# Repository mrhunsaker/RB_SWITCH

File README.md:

# RB Switch

The RB Switch is a three-button Bluetooth Low Energy (BLE) accessibility switch. It presents itself to a computer, tablet, or phone as a standard Bluetooth keyboard, so it works with Switch Control (iOS/iPadOS), Switch Access (Android), and any app that accepts keyboard input.

## At a glance

| | |
|---|---|
| **Buttons** | SW1 Left Arrow, SW2 Enter, SW3 Right Arrow |
| **Bluetooth name** | RB Switch |
| **Microcontroller** | ESP32-S3-MINI-1-N4R2 |
| **Power** | USB-C or a single-cell Li-Po battery. No power switch and no sleep mode. |
| **Charging** | MCP73831, about 500 mA. D1 lights while charging. |
| **Regulator** | TPS63001 3.3 V buck-boost |
| **PCB** | KiCad 10, 4 layers, 115 × 38 mm |
| **Firmware** | Arduino sketch using NimBLE-Arduino 2.x |

## Quick start

1. Power the switch from USB-C or its battery.
2. Pair **RB Switch** in the device's Bluetooth settings.
3. Press each button in a text field: Left, Enter, Right.
4. Set up Switch Control (iOS/iPadOS) or Switch Access (Android) from the guides below.

**Important for Android users:** Android's Switch Access is a separate app you install/update from the Google Play Store, and its setup wizard only offers a one-switch or two-switch configuration. It does not offer a third switch by default. Using the RB Switch's third button on Android requires one extra step beyond the wizard. This is different from iOS/iPadOS, where all three buttons can be assigned directly in the normal setup flow. See [Android Switch Access](docs/switch-access-android.md) and [iOS/iPadOS Switch Control](docs/switch-control-ios.md) before you configure a device.

## Production firmware

The production firmware is:

`firmware/RB_SWITCH_firmware/RB_SWITCH_firmware.ino`

### Button mapping

| Switch | GPIO   | Keyboard key |
| ------ | ------:| ------------ |
| SW1    | GPIO10 | Left Arrow   |
| SW2    | GPIO11 | Enter        |
| SW3    | GPIO12 | Right Arrow  |

Each button press produces one key press followed by one key release. Holding a button does not repeat the key. A press made while no host is connected is ignored.

### Building the firmware

1. Install the Arduino IDE, the **ESP32 Arduino core** by Espressif, and **NimBLE-Arduino 2.x**.
2. Select **ESP32S3 Dev Module** and set **USB CDC On Boot** to **Enabled**.
3. Open the `.ino` file, click **Verify**, then **Upload** over a data-capable USB-C cable. If the upload does not start, hold BOOT, tap RESET, release BOOT.
4. Open the Serial Monitor at 115200 baud.

See [Firmware](docs/firmware.md) for details.

## Documentation

| For | Read |
|---|---|
| Classroom staff setting up a device | [Setup & Pairing](docs/setup.md) |
| iPad and iPhone | [iOS/iPadOS Switch Control](docs/switch-control-ios.md) |
| Android phones and tablets | [Android Switch Access](docs/switch-access-android.md) |
| How the buttons behave | [Switch Operation](docs/use.md) |
| Something is not working | [Troubleshooting](docs/troubleshooting.md) |
| Evaluating a student for switch access and teaching switch skills | [Switch Evaluation Package](docs/evaluation-package.md) |
| Programming the board | [Firmware](docs/firmware.md), [Firmware Customization](docs/firmware-customization.md) |
| Hardware reference | [Hardware](docs/hardware.md) |
| Enclosure label | [QR Code](docs/qr-code.md) |

Published documentation: <https://mrhunsaker.github.io/RB_SWITCH/>

Two printable Word documents are also available. Both are generated from the matching page in `docs/`.

| Download | Source page | Use |
|---|---|---|
| [`RB_Switch_Paraprofessional_Setup_Guide.docx`](RB_Switch_Paraprofessional_Setup_Guide.docx) | `docs/setup.md` | Classroom quick-reference for pairing, setup and troubleshooting |
| [`RB_Switch_Evaluation_Package.docx`](RB_Switch_Evaluation_Package.docx) | `docs/evaluation-package.md` | Fill-in package for evaluating, teaching and documenting adaptive switch access (checklists, five-stage data sheets, graphing sheet, summary report, IEP goal bank) |

## Troubleshooting at a glance

| Symptom | First thing to try |
|---|---|
| Not in the Bluetooth list | Check power; turn Bluetooth off on other nearby devices that were paired before |
| Listed but will not connect | Forget RB Switch on the device and pair again |
| Connected, but no button works | Check it still shows Connected; a press made while disconnected is lost |
| Only two buttons work on Android | Assign the third switch under Assign switches for scanning |
| Will not power on | Charge from USB-C for 30 minutes with a known-good cable |
| Upload fails or no serial port | Hold BOOT, tap RESET, release BOOT; use a data cable |

The full guide, including board-level checks for technicians, is in [Troubleshooting](docs/troubleshooting.md).

## Hardware

The current board uses:

- ESP32-S3-MINI-1-N4R2
- Three Omron B3F-series tactile switches
- USB-C power/programming connection (native USB, no USB-to-serial chip)
- Single-cell Li-Po battery connection and MCP73831 charger
- TPS63001 3.3 V buck-boost regulator
- Battery-voltage sensing (not yet used by the firmware)
- MCP73831 charge-status LED
- Reset and boot buttons, with a 10 kΩ pull-up and 1 µF capacitor on the reset line

Hardware source files are in `electrical/`, `bom/`, and `mechanical/`.

| Path | Contents |
|---|---|
| `electrical/mechanical_switch/RB_Switch.kicad_sch`, `.kicad_pcb` | Current KiCad 10 schematic and 4-layer PCB. The schematic is fully wired and its netlist matches the PCB. |
| `electrical/mechanical_switch/VERIFICATION.md` | How the board was checked against the firmware, and what was not checked |
| `electrical/mechanical_switch/net_table.json` | Net-by-net list of pads |
| `bom/` | BOMs and placement files for JLCPCB and PCBWay, plus sourcing notes |
| `mechanical/` | Enclosure (OpenSCAD) |
| `docs/hardware.md` | Pin map and a part-by-part description of the connections |

> **Before ordering boards:** the files in `electrical/mechanical_switch/gerbers/` and the PCB images in `electrical/mechanical_switch/diagrams/` come from an earlier layout. Re-export them with `create_gerber.ps1` and check the CPL orientation of U1, REG1, D1, J_USB1, and L1 in the fab's preview.

## Production scope

The production design has three mechanical switch inputs only. It does not implement touch sensors, proximity sensors, NeoPixel/RGB indicators, mono-jack inputs, or the earlier F-key input mapping.

The charge-status LED (D1) is controlled by the battery charger and is not a programmable RGB LED.

## Repository layout

| Path | Contents |
|---|---|
| `firmware/RB_SWITCH_firmware/` | Production sketch |
| `firmware/BLE_ADAPTIVE_SWITCH_EXPANDED_SCAFFOLD/` | Archived earlier firmware, not production |
| `electrical/` | KiCad project, gerbers, diagrams, verification notes |
| `bom/` | BOM, placement and sourcing files |
| `mechanical/` | Enclosure and storage box models |
| `docs/` | GitHub Pages source |
| `documents/` | Packaging-friendly copy of `docs/` |
| `tools/` | Scripts that keep `documents/` and the printable Word documents in sync with `docs/` |
| `RB_Switch_Paraprofessional_Setup_Guide.docx` | Printable classroom guide |
| `RB_Switch_Evaluation_Package.docx` | Printable switch evaluation package |
| `CHANGES.md` | Changelog |

## Documentation source

`docs/` is the published GitHub Pages source.

`documents/` contains the same documentation in a packaging-friendly directory. Keep the two documentation sets synchronized when documentation changes.

After editing `docs/`, run:

```
python3 tools/sync_documents.py
node tools/build_docx.js
```

The first script rewrites `documents/` from `docs/`. The second rebuilds both Word documents (`RB_Switch_Paraprofessional_Setup_Guide.docx` from `docs/setup.md` and `RB_Switch_Evaluation_Package.docx` from `docs/evaluation-package.md`). It needs Node.js and the `docx` package (`npm install docx`). Pass `setup` or `evaluation` to build just one. See [tools/README.md](tools/README.md).

## GitHub Pages and enclosure QR code

Publish `docs/` with GitHub Pages. The enclosure QR code should point to the published documentation home page. See [QR Code](docs/qr-code.md).

## Contributing

Contributions to firmware, hardware, and documentation are welcome. See [CONTRIBUTING.md](CONTRIBUTING.md) for project structure, how to propose a change, and pull request expectations, and [CODE_STYLE.md](CODE_STYLE.md) for formatting and naming conventions. Please review [CODE_OF_CONDUCT.md](CODE_OF_CONDUCT.md) before participating.

## Security

To report a suspected security or safety issue, see [SECURITY.md](SECURITY.md) rather than opening a public issue.

## Changelog

See [CHANGES.md](CHANGES.md) for a history of notable changes.

## License

This project is licensed under the APACHE 2.0 License— see [LICENSE](LICENSE) for the full text, including a note on hardware-specific licensing alternatives.

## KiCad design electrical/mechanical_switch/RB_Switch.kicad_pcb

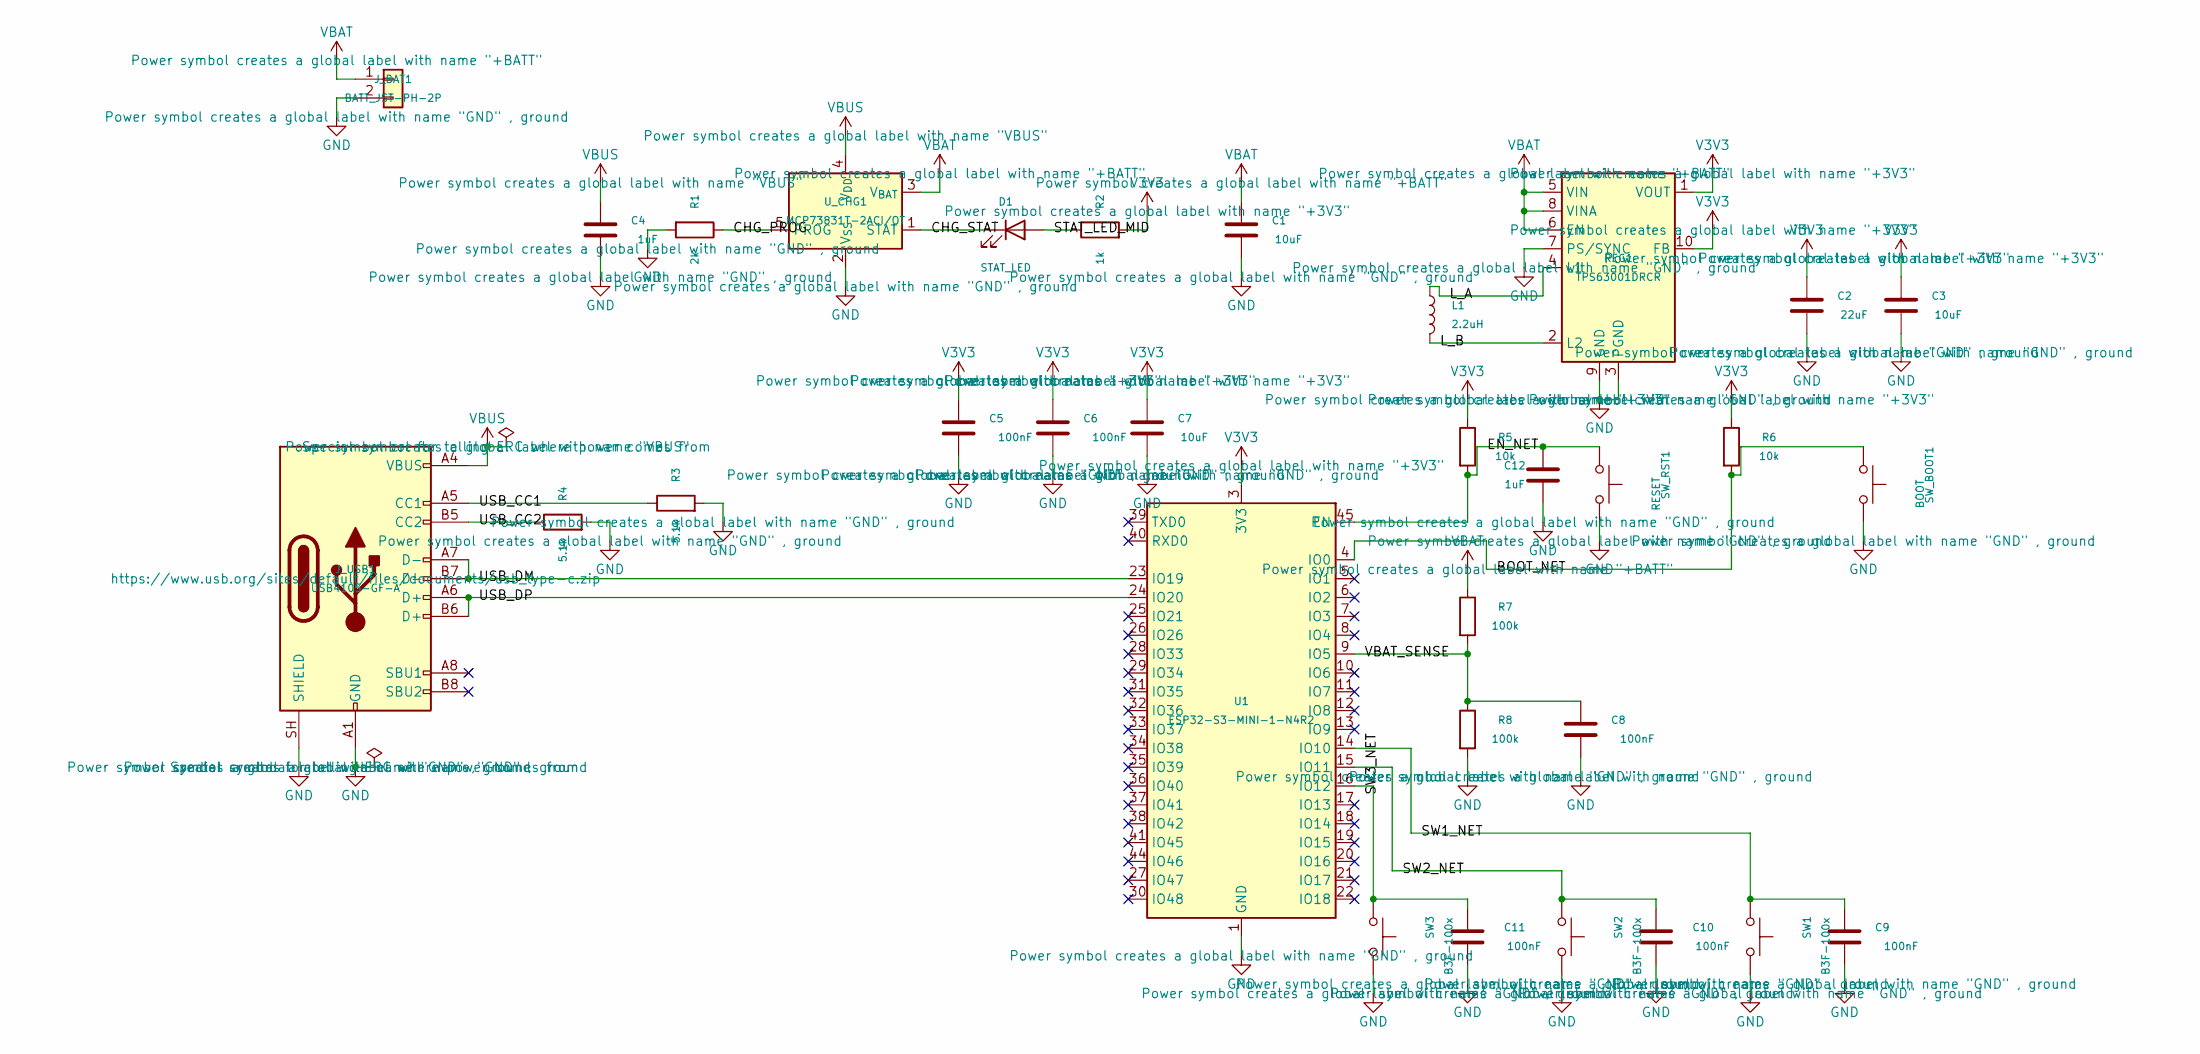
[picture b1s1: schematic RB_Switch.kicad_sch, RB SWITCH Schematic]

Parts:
C1, C3, C7: 10uF; C_0603_1608Metric
C2: 22uF; C_0603_1608Metric
C4, C12: 1uF; C_0603_1608Metric
C5, C6, C8, C9, C10, C11: 100nF; C_0603_1608Metric
D1: STAT_LED; LED_0603_1608Metric
J_BAT1: BATT_JST-PH-2P; JST_PH_S2B-PH-K_1x02_P2.00mm_Horizontal
J_USB1: USB4105-GF-A; USB_C_Receptacle_GCT_USB4105-xx-A_16P_TopMnt_Horizontal
L1: 2.2uH; L_Bourns-SRN4018
R1: 2k; R_0603_1608Metric
R2: 1k; R_0603_1608Metric
R3, R4: 5.1k; R_0603_1608Metric
R5, R6: 10k; R_0603_1608Metric
R7, R8: 100k; R_0603_1608Metric
REG1: TPS63001DRCR; Texas_DRC0010J
SW1, SW2, SW3: B3F-100x; SW_TH_Tactile_Omron_B3F-100x
SW_BOOT1: BOOT; SW_SPST_B3U-1000P
SW_RST1: RESET; SW_SPST_B3U-1000P
U1: ESP32-S3-MINI-1-N4R2; ESP32-S2-MINI-1
U_CHG1: MCP73831T-2ACI/OT; SOT-23-5

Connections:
/BOOT_NET: R6.2, SW_BOOT1.1, U1.4 (IO0)
/CHG_PROG: R1.1, U_CHG1.5 (PROG)
/CHG_STAT: D1.1 (K), U_CHG1.1 (STAT)
/EN_NET: C12.1, R5.2, SW_RST1.1, U1.45 (EN)
/L_A: L1.1, REG1.4 (L1)
/L_B: L1.2, REG1.2 (L2)
/STAT_LED_MID: D1.2 (A), R2.1
/SW1_NET: C9.1, SW1.1, U1.14 (IO10)
/SW2_NET: C10.1, SW2.1, U1.15 (IO11)
/SW3_NET: C11.1, SW3.1, U1.16 (IO12)
/USB_CC1: J_USB1.A5 (CC1), R3.1
/USB_CC2: J_USB1.B5 (CC2), R4.1
/USB_DM: J_USB1.A7 (D-), J_USB1.B7 (D-), U1.23 (IO19)
/USB_DP: J_USB1.A6 (D+), J_USB1.B6 (D+), U1.24 (IO20)
/VBAT_SENSE: C8.1, R7.2, R8.1, U1.9 (IO5)
GND: C1.2, C2.2, C3.2, C4.2, C5.2, C6.2, C7.2, C8.2, C9.2, C10.2, C11.2, C12.2, J_BAT1.2, J_USB1.A1 (GND), J_USB1.A12 (GND), J_USB1.B1 (GND), J_USB1.B12 (GND), J_USB1.SH (SHIELD), R1.2, R3.2, R4.2, R8.2, REG1.3 (PGND), REG1.7 (PS/SYNC), REG1.9 (GND), REG1.11 (PGND), SW1.2, SW2.2, SW3.2, SW_BOOT1.2, SW_RST1.2, U1.1 (GND), U1.2 (GND), U1.42 (GND), U1.43 (GND), U1.46 (GND), U1.47 (GND), U1.48 (GND), U1.49 (GND), U1.50 (GND), U1.51 (GND), U1.52 (GND), U1.53 (GND), U1.54 (GND), U1.55 (GND), U1.56 (GND), U1.57 (GND), U1.58 (GND), U1.59 (GND), U1.60 (GND), U1.61 (GND), U1.62 (GND), U1.63 (GND), U1.64 (GND), U1.65 (GND), U_CHG1.2 (V_{SS})
V3V3: C2.1, C3.1, C5.1, C6.1, C7.1, R2.2, R5.1, R6.1, REG1.1 (VOUT), REG1.10 (FB), U1.3 (3V3)
VBAT: C1.1, J_BAT1.1, R7.1, REG1.5 (VIN), REG1.6 (EN), REG1.8 (VINA), U_CHG1.3 (V_{BAT})
VBUS: C4.1, J_USB1.A4 (VBUS), J_USB1.A9 (VBUS), J_USB1.B4 (VBUS), J_USB1.B9 (VBUS), U_CHG1.4 (V_{DD})

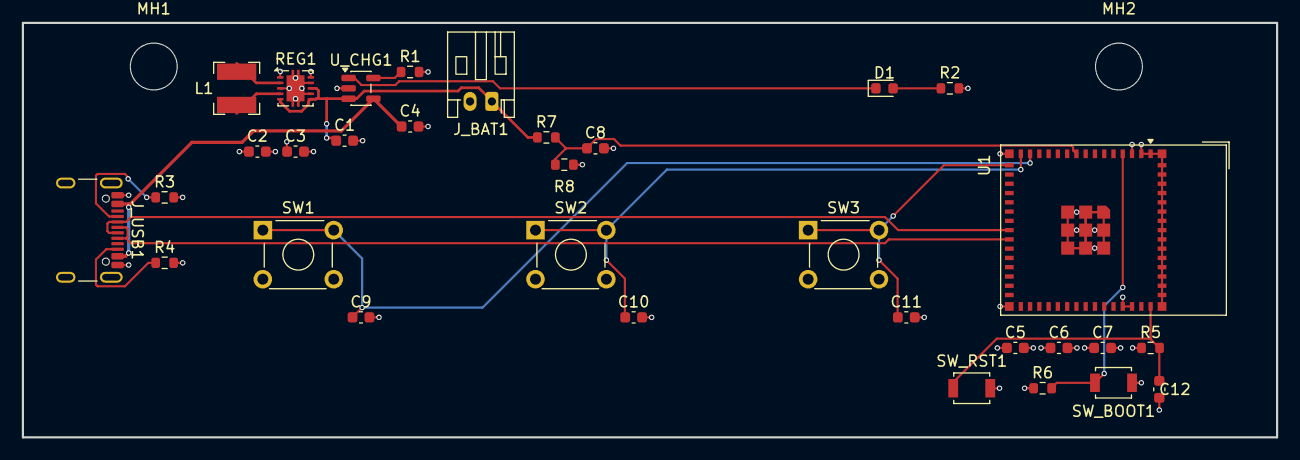
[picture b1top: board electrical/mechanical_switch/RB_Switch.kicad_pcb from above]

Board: 4 copper layers, 115.0 x 38.0 mm, 34 parts (0 on the bottom side), 19 nets.

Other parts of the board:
MH1, MH2: MountingHole; MountingHole_4.3mm_M4

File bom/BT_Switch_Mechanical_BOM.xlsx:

Ref Des | Description | Manufacturer | Part Number | Package / Footprint | Qty | Notes
CORE / MCU
U1 | MCU module — WiFi/BLE SoC, 4MB flash, 2MB PSRAM | Espressif | ESP32-S3-MINI-1-N4R2 | SMD castellated module (RF_Module:ESP32-S2-MINI-1 land pattern) | 1 | Land pattern shared with ESP32-S2-MINI-1 per Espressif; confirmed in KiCad foot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
POWER — REGULATION & CHARGING
REG1 | Buck-boost regulator, fixed 3.3V out, 1.7A switch current | Texas Instruments | TPS63001DRCR | VSON-10 (Package_SON:Texas_DRC0010J_ThermalVias) | 1 | Single-cell Li-ion buck-boost; handles ESP32-S3 BLE TX current peaks with margi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
U_CHG | Li-ion linear charge management IC, USB input | Microchip | MCP73831T-2ACI/OT | SOT-23-5 | 1 | ADDED vs. original BOM — battery + USB-C strongly implies charging; flagged as 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
L1 | Inductor, 2.2uH, shielded | Bourns | SRN4018-2R2Y | SMD 4x4mm | 1 | Buck-boost inductor (single inductor, L1/L2 pins of REG1).
D1 | Charge-status LED | Generic (e.g. Kingbright) | APT2012xx-series or equiv. | 0603 SMD | 1 | Lit while charging (STAT pin, open-drain).
C1 | Capacitor, 10uF, X5R, 10V | Generic | — | 0603 | 1 | REG1 input.
C2 | Capacitor, 22uF, X5R, 10V | Generic | — | 0805 (may not fit 0603 at this voltage rating) | 1 | REG1 output; confirm 0603 X5R 22uF/10V availability, else use 0805.
C3 | Capacitor, 10uF, X5R, 10V | Generic | — | 0603 | 1 | 3V3 rail bulk decoupling.
C4 | Capacitor, 1uF, X5R, 10V | Generic | — | 0603 | 1 | Charger VBUS input decoupling.
R1 | Resistor, 2k, 1% | Generic | — | 0603 | 1 | Sets MCP73831 charge current to 500mA (I=1000V/R_PROG).
R2 | Resistor, 1k | Generic | — | 0603 | 1 | STAT LED current limit.
USB-C PORT
J_USB | USB-C receptacle, 16-pin, mid-mount, low profile | GCT | USB4105-GF-A | SMD 16-pin (Connector_USB:USB_C_Receptacle_GCT_USB4105-xx-A_16P_TopMnt_Horizont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 | 1 | D+/D- wired to ESP32-S3 native USB (no separate USB-UART bridge IC needed).
R3, R4 | Resistor, 5.1k, 1% | Generic | — | 0603 | 2 | CC1/CC2 pulldowns — configures port as a default 5V/500mA-3A USB-C sink.
BATTERY
J_BAT | Battery connector, JST-PH, 2-pin, side-entry | JST | S2B-PH-K-S | Connector_JST:JST_PH_S2B-PH-K_1x02_P2.00mm_Horizontal | 1
R7, R8 | Resistor, 100k, 1% | Generic | — | 0603 | 2 | Battery voltage sense divider (÷2) for ADC monitoring on GPIO5.
C8 | Capacitor, 100nF | Generic | — | 0603 | 1 | ADC sense filter.
BT1 | Li-Po battery pack, 3.7V nominal, ~3000mAh, JST-PH 2-pin | MakerFocus (or equiv.) | TBD — exact purchased SKU | 65 x 36 x 10mm envelope (per COMPONENT_DIMENSIONS) | 1 | OPEN ITEM: confirm exact purchased part — connector polarity/pinout and onboard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
MCU SUPPORT
C5, C6 | Capacitor, 100nF | Generic | — | 0603 | 2 | ESP32-S3 3V3 decoupling.
C7 | Capacitor, 10uF | Generic | — | 0603 | 1 | ESP32-S3 3V3 bulk decoupling.
R5 | Resistor, 10k | Generic | — | 0603 | 1 | EN pull-up.
R6 | Resistor, 10k | Generic | — | 0603 | 1 | GPIO0 (BOOT) pull-up.
SW_RST | Tactile switch, low-profile SMD | Omron | B3U-1000P | SMD (Button_Switch_SMD:SW_SPST_B3U-1000P) | 1 | Manual reset.
SW_BOOT | Tactile switch, low-profile SMD | Omron | B3U-1000P | SMD (Button_Switch_SMD:SW_SPST_B3U-1000P) | 1 | Manual download-mode entry.
STUDENT-FACING SWITCHES (the click)
SW1, SW2, SW3 | Tactile switch, THT, metal-dome click, 6x6mm | Omron | B3F-1000 (or B3F-4050 for higher actuation force) | THT (Button_Switch_THT:SW_TH_Tactile_Omron_B3F-10xx) | 3 | OPEN ITEM: confirm exact force-grade suffix against target students' motor rang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
C9, C10, C11 | Capacitor, 100nF | Generic | — | 0603 | 3 | Debounce/ESD filtering on each switch input.
PCB & FASTENERS
PCB1 | 4-layer PCB, 115 x 38mm, 1.0mm thick, ENIG or HASL | Any capable fab (e.g. JLCPCB) | Per Gerbers in electrical/mechanical_switch/gerbers/ | 0.15mm/0.15mm trace/space | 1
MH1, MH2 | M4 self-tapping screw, ~8mm length | Generic (McMaster, etc.) | M4 x 8mm, pan or button head, plastic self-tap thread | — | 2 | Registers PCB to enclosure at the front-edge mounting holes; also the primary c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
ENCLOSURE (3D printed)
ENC-BASE | Enclosure base, 3D printed | In-house print | BT_Switch_Mechanical_base_RevD2.stl | PETG recommended (impact resistance for classroom use) | 1
ENC-LID | Enclosure lid, 3D printed | In-house print | BT_Switch_Mechanical_lid_RevD2.stl | PETG | 1
ENC-BAR | Button cap / captive bar, 3D printed | In-house print | BT_Switch_Mechanical_bar_RevD2.stl | PETG (or a more flexible filament like TPU for a softer button feel) | 3 | One per switch position.
Highlighted rows = open item, needs confirmation before ordering/printing.

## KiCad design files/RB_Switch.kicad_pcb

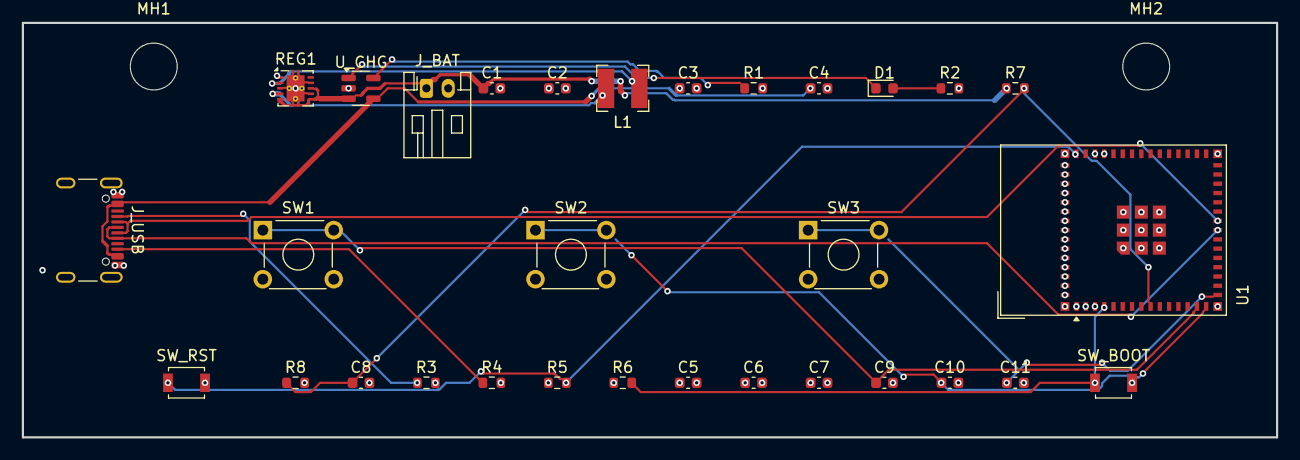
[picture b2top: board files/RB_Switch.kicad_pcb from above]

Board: 4 copper layers, 115.0 x 38.0 mm, 33 parts (0 on the bottom side), 19 nets.

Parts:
C1, C2, C3, C4, C5, C6, C7, C8, C9, C10, C11: C_0603_1608Metric
D1: LED_0603_1608Metric
J_BAT: JST_PH_S2B-PH-K_1x02_P2.00mm_Horizontal
J_USB: USB_C_Receptacle_GCT_USB4105-xx-A_16P_TopMnt_Hori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; USB_C_Receptacle_GCT_USB4105-xx-A_16P_TopMnt_Horizontal
L1: L_Bourns-SRN4018
MH1, MH2: MountingHole_4.3mm_M4
R1, R2, R3, R4, R5, R6, R7, R8: R_0603_1608Metric
REG1: Texas_DRC0010J_ThermalVias
SW1, SW2, SW3: SW_TH_Tactile_Omron_B3F-10xx
SW_BOOT: SW_SPST_B3U-1000P
SW_RST: SW_SPST_B3U-1000P
U1: ESP32-S2-MINI-1
U_CHG: SOT-23-5

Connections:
BOOT_NET: R6.2, SW_BOOT.1, U1.4
CHG_PROG: R1.1, U_CHG.5
CHG_STAT: D1.1, U_CHG.1
EN_NET: R5.2, SW_RST.1, U1.45
GND: C1.2, C2.2, C3.2, C4.2, C5.2, C6.2, C7.2, C8.2, C9.2, C10.2, C11.2, J_BAT.2, J_USB.A1, J_USB.A12, J_USB.B1, J_USB.B12, J_USB.S1, R1.2, R3.2, R4.2, R8.2, REG1.3, REG1.7, REG1.9, REG1.11, SW1.2, SW2.2, SW3.2, SW_BOOT.2, SW_RST.2, U1.1, U1.2, U1.42, U1.43, U1.46, U1.47, U1.48, U1.49, U1.50, U1.51, U1.52, U1.53, U1.54, U1.55, U1.56, U1.57, U1.58, U1.59, U1.60, U1.61, U1.62, U1.63, U1.64, U1.65, U_CHG.2
L_A: L1.1, REG1.4
L_B: L1.2, REG1.2
STAT_LED_MID: D1.2, R2.1
SW1_NET: C9.1, SW1.1, U1.14
SW2_NET: C10.1, SW2.1, U1.15
SW3_NET: C11.1, SW3.1, U1.16
USB_CC1: J_USB.A5, R3.1
USB_CC2: J_USB.B5, R4.1
USB_DM: J_USB.A6, J_USB.B6, U1.23
USB_DP: J_USB.A7, J_USB.B7, U1.24
V3V3: C2.1, C3.1, C5.1, C6.1, C7.1, R2.2, R5.1, R6.1, REG1.1, U1.3
VBAT: C1.1, J_BAT.1, R7.1, REG1.5, REG1.6, REG1.8, U_CHG.3
VBAT_SENSE: C8.1, R7.2, R8.1, U1.9
VBUS: C4.1, J_USB.A4, J_USB.A9, J_USB.B4, J_USB.B9, U_CHG.4

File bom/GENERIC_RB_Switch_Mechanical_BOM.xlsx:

Ref Des | Description | Manufacturer | Part Number | Package / Footprint | Qty | Notes
CORE / MCU
U1 | MCU module — WiFi/BLE SoC, 4MB flash, 2MB PSRAM | Espressif | ESP32-S3-MINI-1-N4R2 | SMD castellated module (RF_Module:ESP32-S2-MINI-1 land pattern) | 1 | Land pattern shared with ESP32-S2-MINI-1 per Espressif; confirmed in KiCad foot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
POWER — REGULATION & CHARGING
REG1 | Buck-boost regulator, fixed 3.3V out, 1.7A switch current | Texas Instruments | TPS63001DRCR | VSON-10 (Package_SON:Texas_DRC0010J_ThermalVias) | 1 | Single-cell Li-ion buck-boost; handles ESP32-S3 BLE TX current peaks with margi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
U_CHG | Li-ion linear charge management IC, USB input | Microchip | MCP73831T-2ACI/OT | SOT-23-5 | 1 | ADDED vs. original BOM — battery + USB-C strongly implies charging; flagged as 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
L1 | Inductor, 2.2uH, shielded | Bourns | SRN4018-2R2Y | SMD 4x4mm | 1 | Buck-boost inductor (single inductor, L1/L2 pins of REG1).
D1 | Charge-status LED | Generic (e.g. Kingbright) | APT2012xx-series or equiv. | 0603 SMD | 1 | Lit while charging (STAT pin, open-drain).
C1 | Capacitor, 10uF, X5R, 10V | Generic | — | 0603 | 1 | REG1 input.
C2 | Capacitor, 22uF, X5R, 10V | Generic | — | 0805 (may not fit 0603 at this voltage rating) | 1 | REG1 output; confirm 0603 X5R 22uF/10V availability, else use 0805.
C3 | Capacitor, 10uF, X5R, 10V | Generic | — | 0603 | 1 | 3V3 rail bulk decoupling.
C4 | Capacitor, 1uF, X5R, 10V | Generic | — | 0603 | 1 | Charger VBUS input decoupling.
R1 | Resistor, 2k, 1% | Generic | — | 0603 | 1 | Sets MCP73831 charge current to 500mA (I=1000V/R_PROG).
R2 | Resistor, 1k | Generic | — | 0603 | 1 | STAT LED current limit.
USB-C PORT
J_USB | USB-C receptacle, 16-pin, mid-mount, low profile | GCT | USB4105-GF-A | SMD 16-pin (Connector_USB:USB_C_Receptacle_GCT_USB4105-xx-A_16P_TopMnt_Horizont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 | 1 | D+/D- wired to ESP32-S3 native USB (no separate USB-UART bridge IC needed).
R3, R4 | Resistor, 5.1k, 1% | Generic | — | 0603 | 2 | CC1/CC2 pulldowns — configures port as a default 5V/500mA-3A USB-C sink.
BATTERY
J_BAT | Battery connector, JST-PH, 2-pin, side-entry | JST | S2B-PH-K-S | Connector_JST:JST_PH_S2B-PH-K_1x02_P2.00mm_Horizontal | 1
R7, R8 | Resistor, 100k, 1% | Generic | — | 0603 | 2 | Battery voltage sense divider (÷2) for ADC monitoring on GPIO5.
C8 | Capacitor, 100nF | Generic | — | 0603 | 1 | ADC sense filter.
BT1 | Li-Po battery pack, 3.7V nominal, ~3000mAh, JST-PH 2-pin | MakerFocus (or equiv.) | TBD — exact purchased SKU | 65 x 36 x 10mm envelope (per COMPONENT_DIMENSIONS) | 1 | OPEN ITEM: confirm exact purchased part — connector polarity/pinout and onboard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
MCU SUPPORT
C5, C6 | Capacitor, 100nF | Generic | — | 0603 | 2 | ESP32-S3 3V3 decoupling.
C7 | Capacitor, 10uF | Generic | — | 0603 | 1 | ESP32-S3 3V3 bulk decoupling.
R5 | Resistor, 10k | Generic | — | 0603 | 1 | EN pull-up.
R6 | Resistor, 10k | Generic | — | 0603 | 1 | GPIO0 (BOOT) pull-up.
SW_RST | Tactile switch, low-profile SMD | Omron | B3U-1000P | SMD (Button_Switch_SMD:SW_SPST_B3U-1000P) | 1 | Manual reset.
SW_BOOT | Tactile switch, low-profile SMD | Omron | B3U-1000P | SMD (Button_Switch_SMD:SW_SPST_B3U-1000P) | 1 | Manual download-mode entry.
STUDENT-FACING SWITCHES (the click)
SW1, SW2, SW3 | Tactile switch, THT, metal-dome click, 6x6mm | Omron | B3F-1000 | THT (Button_Switch_THT:SW_TH_Tactile_Omron_B3F-10xx) | 3 | OPEN ITEM: confirm exact force-grade suffix against target students' motor rang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
C9, C10, C11 | Capacitor, 100nF | Generic | — | 0603 | 3 | Debounce/ESD filtering on each switch input.
PCB & FASTENERS
PCB1 | 4-layer PCB, 115 x 38mm, 1.0mm thick, ENIG or HASL | Any capable fab (e.g. JLCPCB) | Per Gerbers in electrical/mechanical_switch/gerbers/ | 0.15mm/0.15mm trace/space | 1
MH1, MH2 | M4 self-tapping screw, ~8mm length | Generic (McMaster, etc.) | M4 x 8mm, pan or button head, plastic self-tap thread | — | 2 | Registers PCB to enclosure at the front-edge mounting holes; also the primary c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
ENCLOSURE (3D printed)
ENC-BASE | Enclosure base, 3D printed | In-house print | BT_Switch_Mechanical_base_RevD2.stl | PETG recommended (impact resistance for classroom use) | 1
ENC-LID | Enclosure lid, 3D printed | In-house print | BT_Switch_Mechanical_lid_RevD2.stl | PETG | 1
ENC-BAR | Button cap / captive bar, 3D printed | In-house print | BT_Switch_Mechanical_bar_RevD2.stl | PETG (or a more flexible filament like TPU for a softer button feel) | 3 | One per switch position.

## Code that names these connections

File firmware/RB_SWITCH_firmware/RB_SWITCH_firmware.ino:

/*
 * RB_SWITCH_firmware.ino
 *
 * RB Switch - production firmware for the three-button mechanical-switch PCB
 * (RevD/RevD2 hardware; pin map matches the current KiCad schematic and PCB).
 *
 * Hardware inputs:
 *   SW1 -> GPIO10 -> Left Arrow
 *   SW2 -> GPIO11 -> Enter
 *   SW3 -> GPIO12 -> Right Arrow
 *
 * The switches are wired from the GPIO to GND. Each input therefore uses
 * INPUT_PULLUP and is considered active when the GPIO reads LOW.
 *
 * The device presents itself as a standard BLE HID keyboard using NimBLE.
 * Each switch produces one press/release event on the activation edge.
 *
 * Deliberately NOT included:
 *   - TTP223 touch sensors
 *   - proximity / I2C sensors
 *   - NeoPixel / RGB LED control
 *   - mono-jack inputs
 *   - unused expansion inputs
 *
 * Board target:
 *   ESP32-S3 module used by the project (select "ESP32S3 Dev Module"
 *   in Arduino IDE unless your board package/project build process specifies
 *   an equivalent ESP32-S3 target).
 *
 * Modifying this file (remapping keys, changing debounce timing, renaming
 * the BLE device, etc.)? See docs/firmware-customization.md for a guided
 * walkthrough and a HID Usage ID reference table before editing the
 * constants below.
 */

#include <Arduino.h>
#include <NimBLEDevice.h>
#include <NimBLEHIDDevice.h>

// -----------------------------------------------------------------------------
// Hardware pin map: matches the KiCad schematic/PCB in
// electrical/mechanical_switch/ (see docs/hardware.md).
//
//   /SW1_NET -> U1 pin 14 (IO10) -> GPIO10
//   /SW2_NET -> U1 pin 15 (IO11) -> GPIO11
//   /SW3_NET -> U1 pin 16 (IO12) -> GPIO12
//
// Other U1 connections on the board (not driven by this firmware):
//   /BOOT_NET    -> U1 pin 4  (IO0)  BOOT button, 10 k pull-up to 3V3
//   /EN_NET      -> U1 pin 45 (EN)   RESET button, 10 k pull-up to 3V3
//   /USB_DM      -> U1 pin 23 (IO19) native USB D-
//   /USB_DP      -> U1 pin 24 (IO20) native USB D+
//   /VBAT_SENSE  -> U1 pin 9  (IO5)  VBAT / 2 divider (100 k + 100 k), 100 nF;
//                                    not read yet, battery level is fixed
//                                    at 100 below.
// The charge-status LED (D1) is driven by the MCP73831, not by a GPIO.
// -----------------------------------------------------------------------------

static constexpr uint8_t SW1_PIN = 10;
static constexpr uint8_t SW2_PIN = 11;
static constexpr uint8_t SW3_PIN = 12;

// USB HID Usage IDs:
//   0x4F = Keyboard Right Arrow
//   0x50 = Keyboard Left Arrow
//   0x28 = Keyboard Return (Enter)
static constexpr uint8_t LEFT_ARROW = 0x50;
static constexpr uint8_t ENTER_KEY = 0x28;
static constexpr uint8_t RIGHT_ARROW = 0x4F;

static constexpr uint32_t DEBOUNCE_MS = 35;

// -----------------------------------------------------------------------------
// BLE HID state
// -----------------------------------------------------------------------------

NimBLEHIDDevice* hid = nullptr;
NimBLECharacteristic* inputReport = nullptr;
bool connected = false;

class ServerCallbacks : public NimBLEServerCallbacks {
  void onConnect(NimBLEServer* server, NimBLEConnInfo& connInfo) override {
    (void)server;
    (void)connInfo;
    connected = true;
    Serial.println("BLE connected");
  }

  void onDisconnect(NimBLEServer* server, NimBLEConnInfo& connInfo, int reason) override {
    (void)server;
    (void)connInfo;
    (void)reason;
    connected = false;
    Serial.println("BLE disconnected; restarting advertising");
    NimBLEDevice::startAdvertising();
  }
};

// -----------------------------------------------------------------------------
// Debounce state
// -----------------------------------------------------------------------------

struct SwitchState {
  uint8_t pin;
  uint8_t key;
  bool rawState;
  bool stableState;
  uint32_t lastChangeMs;
};

SwitchState sw1{ SW1_PIN, LEFT_ARROW, HIGH, HIGH, 0 };
SwitchState sw2{ SW2_PIN, ENTER_KEY, HIGH, HIGH, 0 };
SwitchState sw3{ SW3_PIN, RIGHT_ARROW, HIGH, HIGH, 0 };

// -----------------------------------------------------------------------------
// BLE HID keyboard
// -----------------------------------------------------------------------------

void sendKey(uint8_t keycode) {
  if (!connected) {
    Serial.println("Key ignored: BLE not connected");
    return;
  }

  // Report ID 1 + modifier + reserved + six key slots.
  uint8_t pressReport[9] = {
    0x01,  // Report ID
    0x00,  // No modifier
    0x00,  // Reserved
    keycode,
    0x00, 0x00, 0x00, 0x00, 0x00
  };

  uint8_t releaseReport[9] = {
    0x01,  // Report ID
    0x00,  // No modifier
    0x00,  // Reserved
    0x00, 0x00, 0x00, 0x00, 0x00, 0x00
  };

  inputReport->setValue(pressReport, sizeof(pressReport));
  inputReport->notify();

  delay(20);

  inputReport->setValue(releaseReport, sizeof(releaseReport));
  inputReport->notify();
}

void setupBLE() {
  NimBLEDevice::init("RB Switch");
  NimBLEDevice::setMTU(247);
  NimBLEDevice::setPower(ESP_PWR_LVL_P9);
  NimBLEDevice::setSecurityAuth(true, false, false);

  NimBLEServer* server = NimBLEDevice::createServer();
  server->setCallbacks(new ServerCallbacks());

  hid = new NimBLEHIDDevice(server);
  hid->setManufacturer("RB Switch");
  hid->setPnp(0x01, 0xFFFF, 0x0001, 0x0100);

  inputReport = hid->getInputReport(1);

  // Standard boot-compatible keyboard report:
  //   8 modifier bits
  //   1 reserved byte
  //   6 keycode bytes
  static const uint8_t reportMap[] = {
    0x05, 0x01,  // Usage Page (Generic Desktop)
    0x09, 0x06,  // Usage (Keyboard)
    0xA1, 0x01,  // Collection (Application)
    0x85, 0x01,  //   Report ID (1)

    0x05, 0x07,  //   Usage Page (Keyboard/Keypad)
    0x19, 0xE0,  //   Usage Minimum (Left Control)
    0x29, 0xE7,  //   Usage Maximum (Right GUI)
    0x15, 0x00,  //   Logical Minimum (0)
    0x25, 0x01,  //   Logical Maximum (1)
    0x75, 0x01,  //   Report Size (1)
    0x95, 0x08,  //   Report Count (8)
    0x81, 0x02,  //   Input (Data, Variable, Absolute)

    0x75, 0x08,  //   Report Size (8)
    0x95, 0x01,  //   Report Count (1)
    0x81, 0x01,  //   Input (Constant)

    0x75, 0x08,  //   Report Size (8)
    0x95, 0x06,  //   Report Count (6)
    0x15, 0x00,  //   Logical Minimum (0)
    0x25, 0x73,  //   Logical Maximum (115)
    0x05, 0x07,  //   Usage Page (Keyboard/Keypad)
    0x19, 0x00,  //   Usage Minimum (0)
    0x29, 0x73,  //   Usage Maximum (115)
    0x81, 0x00,  //   Input (Data, Array)

    0xC0  // End Collection
  };

  hid->setReportMap((uint8_t*)reportMap, sizeof(reportMap));
  hid->setBatteryLevel(100);

  NimBLEAdvertising* advertising = NimBLEDevice::getAdvertising();
  NimBLEAdvertisementData advertisementData;
  advertisementData.setFlags(0x06);
  advertisementData.setName("RB Switch");
  advertisementData.addServiceUUID(NimBLEUUID("1812"));  // HID service
  advertising->setAdvertisementData(advertisementData);
  advertising->setMinInterval(32);
  advertising->setMaxInterval(48);
  advertising->start();

  Serial.println("BLE advertising as \"RB Switch\"");
}

// -----------------------------------------------------------------------------
// Switch handling
// -----------------------------------------------------------------------------

void updateSwitch(SwitchState& sw) {
  // Active LOW: HIGH = released, LOW = pressed.
  const bool raw = digitalRead(sw.pin);
  const uint32_t now = millis();

  if (raw != sw.rawState) {
    sw.rawState = raw;
    sw.lastChangeMs = now;
  }

  if ((now - sw.lastChangeMs) >= DEBOUNCE_MS && sw.stableState != sw.rawState) {

    sw.stableState = sw.rawState;

    // Fire only on the transition to pressed.
    if (sw.stableState == LOW) {
      Serial.printf("SW GPIO%u -> HID 0x%02X\n", sw.pin, sw.key);
      sendKey(sw.key);
    }
  }
}

// -----------------------------------------------------------------------------
// Arduino setup / loop
// -----------------------------------------------------------------------------

void setup() {
  Serial.begin(115200);
  delay(250);

  pinMode(SW1_PIN, INPUT_PULLUP);
  pinMode(SW2_PIN, INPUT_PULLUP);
  pinMode(SW3_PIN, INPUT_PULLUP);

  // Initialize debounce states from the actual switch state so a held
  // switch during boot does not generate a phantom transition.
  const uint32_t now = millis();
  sw1.rawState = sw1.stableState = digitalRead(sw1.pin);
  sw2.rawState = sw2.stableState = digitalRead(sw2.pin);
  sw3.rawState = sw3.stableState = digitalRead(sw3.pin);
  sw1.lastChangeMs = now;
  sw2.lastChangeMs = now;
  sw3.lastChangeMs = now;

  Serial.println();
  Serial.println("RB Switch firmware");
  Serial.println("SW1 GPIO10 -> Left Arrow");
  Serial.println("SW2 GPIO11 -> Enter");
  Serial.println("SW3 GPIO12 -> Right Arrow");

  setupBLE();
}

void loop() {
  updateSwitch(sw1);
  updateSwitch(sw2);
  updateSwitch(sw3);
  delay(1);
}

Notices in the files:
README.md:
License: Apache 2.0
